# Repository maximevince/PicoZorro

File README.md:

# PicoZorro

An RP2350 microcontroller on the Amiga **Zorro II** bus. PIO state machines
speak the bus protocol, XRDY inserts wait states while the firmware fetches
the data, and the card's registers appear in the Amiga's address space
through Autoconfig. No CPLD, no FPGA, no level shifters. Open hardware,
open firmware, open drivers.

The first card is the **PicoZorro One**: Ethernet, a USB host port and an
MP3 decoder for an A2000-class Zorro II slot. Its through-hole version, the
**PicoZorro One TH**, is built from off-the-shelf modules and a handful of
through-hole parts, so that anyone with a soldering iron can make one.

| What | How | Amiga side |
|---|---|---|
| Ethernet 10/100 | W5500 module on SPI | `picozorro.device`, a SANA-II driver (Roadshow, AmiTCP, ...) |
| USB host (full speed) | the RP2350's USB port | `picozorrousb.device` for Poseidon |
| MP3 / MP2 decoding | minimp3 on the card | `mpega.library`, a drop-in replacement for the 68k one |
| Boot ROM | the drivers served from the card | nothing to install: Kickstart loads them at boot |
| Firmware updates | A/B partitions in the module's flash | `pzflash` on the Amiga |

## One TH: two builds, one board

The One TH PCB carries two parts lists. Every through-hole part has an SMD
alternate on the same nets, in the same footprint area, and only one of
the two is ever fitted. Same Gerbers, same firmware, same Amiga software.

| DIY build (all through-hole) | JLC build (SMD set assembled by JLCPCB) |
|---|---|
|  |  |
| KiCad's default variant. You solder everything: 1N5817, radial PTC, 2N3904, axial resistor, LD1117V33 in TO-220, electrolytics, a microSD breakout. | KiCad variant `JLC`. JLCPCB places SS14, 1812 PTC, MMBT3904, 0603 resistors, an AMS1117-3.3 (SOT-223) and banks of 22 uF MLCCs, plus a Hirose push-push microSD socket. You solder only the modules on their headers and the USB connector (J2 or J3). |
| Parts list: `fab/picozorro-one-th-parts.csv` | BOM and placement: `fab/jlc/picozorro-one-th-bom-jlc.csv`, `fab/jlc/picozorro-one-th-cpl-jlc.csv` |

Both builds take the same bought modules (Core2350B0, W5500 "Lite", the
optional GY-PCM5102 DAC). The silk frames each through-hole / SMD pair
under one label, so the board reads the same either way. Order options,
the full part-by-part table and the LCSC numbers are in
`hardware/picozorro-one-th/README.md` and `fab/order-notes.txt`.

## Status

- Firmware and drivers run on a prototype (a Core2350B module on a carrier
  board) in an Amiga: Ethernet, USB mass storage, MP3 playback.
- The **PicoZorro One TH** board is designed, routed and passes ERC/DRC.
  It has **not been built yet**. Do not order boards until this says so.
- The default firmware build is the One's image (features `xrdy-direct`,
  `int-nfet`, `usb-host`); the One TH and the One SMD share one pin map
  and one image. The four pins that differ from the prototype
  (microSD chip select, I2S) are unused, and the text log on GPIO46 lands
  on the DAC's bit-clock pin, which is harmless while no DAC is fitted.
- microSD and the I2S DAC are on the board for later; no firmware uses
  them yet.

## Repository

| Path | What |
|---|---|
| `hardware/picozorro-one-th/` | KiCad project, fabrication files, parts list and design notes of the One TH |
| `hardware/lib/` | the PicoZorro KiCad library (the Zorro II edge connector) |
| `hardware/EDGE_CONNECTOR.md`, `hardware/PINMAP.md` | edge-connector orientation with its evidence; the GPIO map |
| `firmware/` | RP2350 firmware in Rust on embassy: `pz-core` (Autoconfig, register window, network model, host tests), `pz-hal`, `pz-app` (the `picozorro` image, `hello`, `nic-demo`, `bus-listen`) |
| `amiga/` | the Amiga drivers, `mpega.library`, `pzflash`, the boot ROM, test and diagnostic tools; built with bebbo's GCC in docker |
| `tools/` | firmware image tools: update file, boot image, flashing |
| `docs/` | the register interface (`REGISTERS.md`, `REGISTERS-USB.md`, `REGISTERS-MPEG.md`), firmware updates (`UPDATE.md`), Zorro II electrical facts |

## From a bare board to a network

1. Build the card: `hardware/picozorro-one-th/README.md` (parts list,
   fabrication files, what to check before the first power-up).

   Steps 2 and 3 can be skipped: each
   [release](https://github.com/maximevince/PicoZorro/releases) carries
   `picozorro-install.uf2`, `picozorro.pzf` and the Amiga software, built
   by CI (`.github/workflows/build.yml`).
2. Build the Amiga software once, it goes into the firmware's boot image:

       make -C amiga toolchain   # once: pulls the image, fetches NDK 3.2 and the Poseidon headers
       make boot                 # drivers + boot ROM -> firmware/boot.img

3. Build and install the firmware, module on the bench, not in the Amiga:

       make fw-uf2               # firmware/picozorro-install.uf2

   Hold BOOTSEL while plugging the module's USB into the PC and copy
   `picozorro-install.uf2` onto the USB drive that appears. With an SWD
   probe, `make fw-install` does the same over SWD. This writes the A/B
   partition layout, so later updates come from the Amiga
   (`docs/UPDATE.md`), no cable needed. The UF2 route has not been
   exercised on a module yet; the SWD route has.
4. Card in the slot, Amiga on. Kickstart finds the card (manufacturer 2011,
   product $5A), loads `picozorro.device`, `picozorrousb.device` and
   `mpega.library` from it. Point your TCP/IP stack at `picozorro.device`
   unit 0 and Poseidon at `picozorrousb.device`: `amiga/README.md`.

Other targets: `make` (host tests + every firmware binary), `make amiga`,
`make fw-uf2 BIN=hello` (a first-light image as UF2), `make check-one-th`
(ERC + DRC). Needs: rustup (stable; the toolchain file adds the target),
arm-none-eabi-gcc (the MP3 decoder is C), picotool, probe-rs with RP2350
support for SWD, cargo-binutils for the update and install files; for `make amiga`:
docker, lha (or 7z), curl. Details in `firmware/README.md` and `amiga/README.md`.

## Safety

The card sits on the CPU bus of a machine that is not made any more.
Open-collector lines (XRDY, /INT2, /INT6) are never driven high. The
edge-connector orientation is documented with its evidence in
`hardware/EDGE_CONNECTOR.md`; check it against your board before powering
anything.

## Why the RP2350 sits on the 5 V bus without level shifters

The Zorro II bus is 5 V TTL. The RP2350's GPIO0-39 are fault-tolerant pads:
Raspberry Pi specifies them to 5.5 V **as long as IOVDD (the chip's 3.3 V)
is powered**. With IOVDD at 0 V the same pad is only rated to 3.63 V, and the
datasheet says a pad above that with IOVDD off will be damaged. So the whole
question is the first milliseconds after switch-on: can the bus be above
3.63 V before the card's 3.3 V regulator has come up?

Reasoning first: the bus drivers and pull-ups are fed from the same +5 V
rail that feeds the card's regulator, so no bus line can be ahead of that
rail. Below regulation an LDO just passes its input minus a drop, so IOVDD
follows the rail closely. The datasheet's limit only bites if the regulator
*delays* its start by more than the time the rail needs to travel from where
the LDO can start (about 2.3 V) to 3.63 V.

Then measured, with a logic analyser's analog channels:

- An Amiga's Zorro +5 V rises to 5.1 V in 3.4 ms; **2.3 V to 3.63 V takes
  about 1 ms**, 3.63 V to 4.2 V another 0.5 ms.
- The Core2350B's regulator (ME6217, 3.3 V), hit with a hard 5 V step on its
  input as the worst case: **3V3 reaches 3 V about 50 us later.**

50 us against 1 ms is a 20x margin, and on the real ramp the regulator does
not even see a step. IOVDD is therefore always above 1.8 V when the bus
passes 3.63 V and above 2.5 V when it passes 4.2 V, which is what the
datasheet's rating table asks for. The silicon on the module is an A4
stepping, the one Raspberry Pi qualified as 5 V tolerant; the erratum that
made A2 parts leak (RP2350-E9) is fixed from A3 on.

What this does **not** cover: hot-plugging a card into a live machine, or a
card whose 3.3 V rail is dead while the bus is up. Both put 5 V on unpowered
pads. Don't.

## Licence

Copyleft on purpose: forks stay open.

- Firmware, tools and the Amiga software: **GPL-3.0-or-later**
  (`LICENSES/GPL-3.0-or-later.txt`). The Rust dependencies (embassy and
  friends, MIT / Apache-2.0) are compatible. Vendored code keeps its own
  licence: `firmware/vendor/`.
- Hardware (`hardware/`): **CERN-OHL-S-2.0**, strongly reciprocal
  (`LICENSES/CERN-OHL-S-2.0.txt`).
  Three of the 3D models in `hardware/picozorro-one-th/3d/` embed parts of
  the KiCad library and are CC BY-SA 4.0 with KiCad's exception
  (`3d/SOURCES.txt`).
- Documentation: **CC BY-SA 4.0** (`LICENSES/CC-BY-SA-4.0.txt`).

Copyright Maxime Vincent.

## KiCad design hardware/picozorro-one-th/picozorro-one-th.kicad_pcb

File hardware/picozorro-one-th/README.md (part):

# PicoZorro One TH

The PicoZorro One is the Zorro II network and USB card of the PicoZorro
project. The One TH is its through-hole version: bought modules and a
handful of through-hole parts on a bare two-layer PCB. Every through-hole
part also has an SMD alternate on the same board, so the same PCB can be
assembled by JLCPCB instead (see "Two builds" below).

- RP2350B: a Waveshare Core2350B0 module (B0 variant, no PSRAM) on four
  2x8 pin strips. Its PIO state machines speak the Zorro II bus directly.
- Ethernet: a W5500 "Lite" module (USR-ES1, WIZnet WIZ850io pinout) on SPI1.
- USB host: the RP2350's own USB port, to a type A receptacle or a PC-style
  2x5 internal header.
- Optional: microSD on SPI1 (a breakout, or a soldered socket on the JLC
  build) and a GY-PCM5102 I2S DAC breakout.

## Status

Rev A. The schematic and the routed board pass KiCad ERC and DRC with zero
violations, DRC with schematic parity (`make check-one-th` at the top of the
repository). **The board has not been built or tested in an Amiga. Do not
order boards yet.** The open points are listed at the end of this file.

## Two builds: DIY through-hole and JLC-assembled

One PCB, two builds. The **DIY build** (KiCad's default variant) fits every
part through-hole, soldered by hand. The **JLC build** (KiCad variant `JLC`)
has JLCPCB place an SMD set, almost all JLC Basic parts; the builder then
solders only the modules on their headers and J2 (or J3).

Each through-hole part and its SMD alternate sit on the same nets and share
the footprint area; the two are never both fitted. The SMD alternate of a
part has the part's number times 100 plus 1, 2, ... as its reference (D101 is
D1's, C101-C103 are C1's bank), because KiCad cannot give one symbol two
footprints. The board hides those references; silk frames group each pair
under one label, and the JLC files name them "D1 (SMD)".

## Files

| Path | What |
|---|---|
| `picozorro-one-th.kicad_pro`, `.kicad_sch`, `.kicad_pcb`, `.kicad_dru` | KiCad 10 project with the variant `JLC`; the edge-connector symbol and footprint come from `../lib` |
| `fab/gerbers/`, `fab/picozorro-one-th-gerbers.zip` | Gerber and Excellon drill files, the same for both builds |
| `fab/picozorro-one-th-parts.csv` | parts list of the DIY build (the SMD alternates show DNP) |
| `fab/jlc/picozorro-one-th-bom-jlc.csv`, `fab/jlc/picozorro-one-th-cpl-jlc.csv` | JLC BOM (the SMD set with LCSC numbers; the through-hole alternates as DNP) and placement file (SMD set only, rotations corrected for JLC) |
| `fab/order-notes.txt` | the options to pick in the order form, and what the builder solders in each build |
| `3d/` | STEP models of the modules and the PTC that the board references; origins and licences in `3d/SOURCES.txt` |
| `images/` | schematic (PDF, PNG), copper and silkscreen views, 3D renders: `pcb-3d-th.png` (DIY build), `pcb-3d-jlc.png` (JLC build, same view), `pcb-3d-iso.png` (DIY build, isometric) |

## What the builder solders

DIY build, everything by hand. The last column names the SMD alternate the
JLC build fits instead (LCSC part number in brackets; JLC Basic parts unless
marked Extended).

| Ref | Part | Value / type | Package | Fitted (DIY) | JLC build alternate |
|---|---|---|---|---|---|
| U1 (P1-P4) | Waveshare Core2350B0 module (no PSRAM) | - | four 2x8 2.54 mm pin strips | yes | same, by hand |
| M1 | W5500 "Lite" module (USR-ES1, WIZ850io pinout) | - | two 1x6 2.54 mm rows | yes | same, by hand |
| M2 | microSD breakout, 3.3 V, no level shifter | - | one 1x6 2.54 mm row | optional | J6, Hirose DM3AT-SF-PEJM5 push-push socket (C114218, Extended), with R2-R5 and C5, C6 |
| M3 | PCM5102A DAC breakout "GY-PCM5102" | - | 1x6 row (signals) + 1x9 row (holding only) | optional | same, by hand (optional) |
| D1 | Schottky diode | 1N5817 | DO-41, 10.16 mm | yes | D101, SS14, SMA (C2480) |
| F1 | resettable PTC fuse, 30 V (or 16 V) family | 0.9 A hold, e.g. Littelfuse RUEF090 | radial, 5.08 mm leads | yes | F101, 1.1 A hold, 1812, Littelfuse 1812L110/33MR (C142747, Extended) |
| C1 | electrolytic capacitor, bus +5 V | 100 uF | radial, D6.3 mm, 2.5 mm pitch | yes | C101-C103, 3 x 22 uF 25 V X5R 1206 (C12891) |
| C2 | electrolytic capacitor, USB port | 220 uF | radial, D8 mm, 3.5 mm pitch | yes | C201-C205, 5 x 22 uF 25 V X5R 1206 (C12891) |
| U2 | 3.3 V regulator for 3V3_AUX | LD1117V33 | TO-220, lying down | yes | U201, AMS1117-3.3, SOT-223, tab = VOUT (C6186) |
| C3 | U2 input capacitor | 10 uF 25 V electrolytic | radial, D5 mm, 2 mm pitch | yes | C301, 10 uF 25 V X5R 0805 (C15850) |
| C4 | U2 output capacitor | 10 uF | disc, 5 mm pitch | yes | R6 1.0 ohm 0603 (C22936) in series with C401 22 uF 1206 (C12891) |
| Q1 | NPN transistor | 2N3904 | TO-92, E-B-C | yes | Q101, MMBT3904, SOT-23, 1 B / 2 E / 3 C (C20526) |
| R1 | resistor, GPIO45 to Q1 base | 2.2 k | axial, DIN0207, 10.16 mm | yes | R101, 2.2 k 0603 (C4190) |
| J2 | USB 2.0 type A receptacle, right angle | Molex 67643 pattern | through-hole | one of J2 / J3 | same, by hand |
| J3 | PC internal USB header | 2x5, pin 9 absent | 2.54 mm header | one of J2 / J3 | same, by hand |
| J4 | SWD header: SWCLK / GND / SWDIO | - | 1x3 2.54 mm | no (developers) | same |
| J5 | recovery header: RUN / GND / BOOTSEL | - | 1x3 2.54 mm | no (recovery) | same |

The JLC build adds, with J6 only: R2-R5, 10 k 0603 pull-ups on DAT2, CMD
(MOSI), DAT0 (MISO) and DAT1 (C25804); C5 100 nF 0603 (C14663) and C6
10 uF 0805 (C15850) at J6's VDD.

U1 must be the B0 variant in both builds: on the B1 / B2 modules GPIO47 is
the PSRAM chip select, and this board needs GPIO47 for the I2S word clock.
The microSD chip select (GPIO18) works on any variant.

The parts lists are `fab/picozorro-one-th-parts.csv` (DIY) and
`fab/jlc/picozorro-one-th-bom-jlc.csv` (JLC).

F1 alternatives: Littelfuse RUEF090 or 30R090U, Bourns MF-R090-0-9,
Littelfuse RUSBF090 (0.07-0.12 ohm new, 0.22 ohm at most after a trip;
holds 0.57-0.61 A at 60 C). Not the 0.5 A hold parts: they hold 0.36 A at
50 C and drop up to 0.59 V. The footprint is KiCad's
`Fuse_Bourns_MF-RHT070` (5.1 mm lead spacing with the 1.2 mm stagger of a
radial PTC's leads, 0.71 mm holes for 0.51 mm leads); the KiCad library
has no footprint for the parts named above.

Q1 alternatives: the footprint is three holes in line, base in the middle,
emitter - base - collector as pins 1-2-3.

| Part | Pin order 1-2-3 | Fits |
|---|---|---|
| 2N3904, PN2222A, 2N4401, S8050 | E-B-C | as drawn |
| BC547, BC548, BC337 | C-B-E | rotated 180 degrees (silkscreen: "BC547 C-B-E: turn round") |

Only the 2N3904 and the BC547 were checked against a data sheet; check the
others before fitting.

U2 alternatives (pin order GND / VOUT / VIN seen from the front, tab =
VOUT): LD1117V33, LM1117T-3.3, AZ1117T-3.3, LM1086CT-3.3, LT1086CT-3.3.
They do not fit with VIN and VOUT swapped, middle pin GND, tab GND: LF33CV,
LM3940IT-3.3, MCP1825S, MCP1826S. The silkscreen names the three holes.
C3 is an electrolytic: mind its polarity.

## Solder jumpers

| Jumper | As delivered | Change |
|---|---|---|
| JP1 | bridged 1-2 by a trace: Q1 collector to /INT2 (J1 pin 19) | cut 1-2 and bridge 2-3 for /INT6 (J1 pin 22) |
| JP2 | **open** in both builds: U2 (DIY) or U201 (JLC) supplies 3V3_AUX | fallback for a board without U2: bridge it, and the module's 3V3 (U1 P2.16) feeds 3V3_AUX. Never bridge it with U2 or U201 fitted |

## Pin map

The PicoZorro GPIO map (`../PINMAP.md`) applies to GPIO0-17, 19-43 and 45.
Four pins differ on this board:

| GPIO | Module pin | Shared map | This board |
|---|---|---|---|
| 18 | P3.6 | /LDS | microSD chip select |
| 44 | P4.15 | /ARM | I2S data (DIN) |
| 46 | P2.4 | UART0 TX | I2S bit clock (BCK) |
| 47 | P2.3 | not connected / PSRAM chip select | I2S word clock (LCK), B0 module only |

The whole map:

| GPIO | Signal | Goes to |
|---|---|---|
| 0-15 | D0-D15 | J1 |
| 16 | /AS | J1 74 |
| 17 | /UDS | J1 72 |
| 18 | SD_CS | M2 pin 2 / J6 DAT3 |
| 19 | READ | J1 68 |
| 20-26 | A1-A7 | J1 |
| 27 | XRDY | J1 18, direct |
| 28-35 | A16-A23 | J1 |
| 36 | /CFGIN | J1 12 |
| 37 | /CFGOUT | J1 11 |
| 38 | /BUSRST | J1 94 |
| 39 | NIC_INT | M1 INTn (the module's LED1 is on the same pin, lit while INTn is high) |
| 40 | SPI1 MISO | M1, M2 / J6 DAT0 |
| 41 | NIC_CS | M1 SCSn |
| 42 | SPI1 SCK | M1, M2 / J6 CLK |
| 43 | SPI1 MOSI | M1, M2 / J6 CMD |
| 44 | I2S_DIN | M3 |
| 45 | INT_DRV | R1 / R101, Q1 / Q101 base |
| 46 | I2S_BCK | M3 |
| 47 | I2S_LCK | M3 |

Bus signals use only GPIO0-38 (5 V tolerant); GPIO39-47 never see the bus.
The bus nets go straight from the edge fingers to the module pins: no series
resistors, no buffers. XRDY comes from GPIO27 directly (36 ns from /AS to
XRDY measured at 240 MHz). The edge connector (J1) has +5 V on pins 5 and
6, all GND pins connected and pin 91 tied to GND.

There is no UART: debug is SWD with RTT on J4.

**/LDS (J1 pin 70) is not connected.** The bus PIO programs wait on /AS and
branch on READ only; the strobes are two bits of the sampled word, used by
the register model to tell word from byte access. With /UDS alone, word
access, Autoconfig (its writes are /UDS-only bytes on D15-D8) and the
rejection of an odd-byte write (/UDS high) work; an even-byte write cannot be
told from a word write and is taken as a word write.

**GPIO47 and the module variant.** On the Core2350B B1 / B2 modules the PSRAM
chip select sits directly on GPIO47 with a 10 k pull-up (R9); R11 (0 R) only
links the net to header pin P2.3. Driving GPIO47 there selects the PSRAM
during flash access. I2S therefore needs the B0 module, and the firmware
must not drive GPIO47 unless a PSRAM probe has found none.

### Firmware

The default firmware build is this board's image: its features
`xrdy-direct` (GPIO27 pulls XRDY) and `int-nfet` (GPIO45 push-pull, high
asserts /INT) match the bus side. The One TH and the One SMD share one pin
map and one image. GPIO18 / 44 / 46 / 47 may only be driven by a firmware
built for this board. The microSD and I2S
drivers are not written yet. When they are:

- SPI1 is shared. The SD card releases its data output one clock after its
  chip select rises, so the firmware clocks one byte with both chip selects
  high before selecting the W5500; each device gets its own SCK rate.
- An SD card that has not been put into SPI mode still listens to the
  command line. The firmware initialises the card before network traffic
  starts; a card inserted later sees W5500 traffic first.
- I2S is enabled only after a PSRAM probe has found none.

## Power

```
J1 +5V --+-- C1 --GND
         |
         +-- D1 -->|-- VIN ---- U1 P2.15 (VBUS: module LDO input)
         |                 +--- M3 VIN
         |
         +-- F1 ---+--- VBUS_PORT --- J2.1, J3.1, J3.2
         |         +--- C2 --GND
         |
         +-- C3 --- U2 --- C4 --- 3V3_AUX --- M1, M2 / J6

U1 P2.16 (3V3, module LDO output) --- JP2 (open; bridged only without U2) --- 3V3_AUX
```

JLC build: D101, F101 and U201 (C301 at its input, R6 + C401 at its output)
in place of D1, F1 and U2 (C3, C4); the bulk is two MLCC banks, C101-C103 on
the bus +5 V for C1 and C201-C205 on VBUS_PORT for C2 (40.9 and 68.2 uF
effective at 5 V). JP2 stays open in both builds.

- **D1** (Schottky) keeps bench power off the Amiga's +5 V rail: the
  module's FPC USB adapter feeds the same VBUS net.
- **F1** (PTC) is all there is between the bus +5 V and the USB port, as on
  PC motherboards (Intel 815E reference board; Intel, "Power Delivery Design
  Issues for Hi-Speed USB on Motherboards") and the fuse-only hobby host
  boards. No series diode (with a Schottky the port sat at about 4.45 V), no
  power switch IC.
- The card is powered by the Amiga, or by the FPC adapter on the bench. The
  port never powers the card.
- Not protected: a hub that feeds its own 5 V back into the port reaches the
  Amiga's +5 V rail through F1, also with the Amiga switched off. USB 2.0
  section 7.2.1 forbids a device to source current on its upstream port.

Port voltage from a 5.0 V rail at 500 mA: 5.0 - 0.06 (F1 new, 0.11 after a
trip) = 4.94 V (4.89 V). USB 2.0 Table 7-7 asks for 4.75 V at a high-power
port, so the rail may sag to 4.86 V. Section 7.2.1.2.1 asks for
resettable over-current protection below 5.0 A: F1 trips at 1.8 A (Intel's
guide sizes a single-port fuse at 1.5 A trip or more). The fault is not
reported to the host stack: there is no pin for it.

### Bulk: C1 and C2

USB 2.0 section 7.2.4.1 asks for no less than 120 uF of low-ESR capacitance
on the downstream VBUS "per hub", to keep the power of the other ports
within 330 mV when a device is plugged in (load model 10 uF with 44 ohm).
This card has one port: the only other load on that VBUS is the card's own
+5 V entry (D1 to VIN, U2) and, behind it, the Amiga rail. So both stay: C1
at the entry, C2 at the port, F1 between them (on a microsecond scale the
PTC is a plain resistor that isolates the two).

A hot-plug simulation (1 m cable, assumed rail and ESR values, not a
measurement) puts the entry droop at 0.23 / 0.15 V (PTC 0.1 / 0.3 ohm) with
the JLC build's ceramic banks, the smallest of the arrangements tried at
0.3 ohm, matched only by a low-ESR polymer 220 uF at the entry (0.22 /
0.17 V). The DIY build's two electrolytics give 0.43 / 0.29 V; a single
ordinary electrolytic at the entry (0.15 ohm ESR) 0.61 / 0.45 V, worse than
either split. The port itself dips 0.4 to 3 V for microseconds whatever is
fitted: no arrangement holds it within 330 mV with a stick plugged straight
in. Both builds lay the two groups out alike: the electrolytic on top, its
MLCC row under it in the 15 mm band.

### 3.3 V

3V3_AUX (M1, M2 / J6) has its own regulator, **U2, fitted in both builds**;
JP2 stays open and the module's LDO feeds only the module. The loads: M1
132 mA typical (W5500 data sheet section 5.4; the WIZ850io module 141 mA),
M2 up to 100 mA, the maximum averaged over 1 s in SPI mode (SD Physical
Layer Simplified Specification v3.01, Table 3-4 note 7; SanDisk's manual
gives 65 mA read and 75 mA write at most). The simplified specification
gives no peak or inrush figure. That is about 0.22 A typical, 0.24-0.27 A
at those ceilings. M3 is not on this rail: its VIN comes from VIN and it has
its own two regulators.

U2 takes the bus +5 V directly, not behind D1. DIY build: LD1117V33. ST
guarantees 3.235-3.365 V out for Vin 4.75-10 V at 0-800 mA (TJ 0-125 C,
LD1117 data sheet DocID2572 Rev 38, Table 6), dropout 1.15 V at most at
500 mA: it regulates from 4.45 V, a 0.30 V margin at the bus's 4.75 V
minimum. The JLC build fits U201, an AMS1117-3.3 (SOT-223, the same pin
order, tab = VOUT) under U2's footprint, its tab on the same 3V3_AUX copper
area. Its only guaranteed dropout is 1.3 V at 800 mA, so it needs 4.60 V: a
margin of about 0.15 V. R6 (1.0 ohm) in series with C401 (22 uF) at its
output gives the ceramic the ESR of the tantalum the AMS1117 data sheet is
written for. Dissipation in either build: (5.25 V - 3.3 V) x 0.3 A = 0.59 W
at most.

- C3, 10 uF at the input in both builds (DIY: 25 V radial electrolytic;
  JLC: C301, 0805 X5R): one value that satisfies the LD1117 (100 nF), the
  LM1117 and AZ1117 (10 uF) and the AMS1117 application circuit (10 uF). C4,
  10 uF at the output (ST's figure; ST gives no ESR window).
- With U2 fitted and the card on bench power only, M1 and M2 are unpowered
  while the module runs.

The module's regulator is the fallback (JP2 bridged on a board without
U2), not the default: the ME6217C33M5G data sheet gives 800 mA as a typical
IOUT(max) (and as the absolute maximum), no minimum, and notes it may not be
reached because of package dissipation; it gives no thermal resistance. Its
sibling ME6207 rates the SOT-23-5 package at 250 mW. The W5500 alone puts
0.25-0.41 W into it, with an SD card 0.45-0.66 W. Measured with a thermal
camera, module plus W5500 on the module's 3V3, room 20 C: nothing on the
module above 40 C (no SD card in that measurement).

There is no extra bulk capacitance on VIN or 3V3: it would slow the 3V3
rise against the Amiga's +5 V ramp.

## /INT driver

Q1, an NPN transistor, drives the interrupt line open collector: emitter to
GND, base through R1 (2.2 k) to GPIO45, collector through JP1 to /INT2
(default) or /INT6. GPIO45 high asserts the interrupt. GPIO45 resets with
its pull-down on, so Q1 is off while the module is in reset; with the module
absent the base is open and Q1 is off. GPIO45 is not 5 V tolerant, so it
cannot pull the bus line itself.

Sizing: a B2000 and an A500+ pull both lines up with 1 k (5 mA at 5 V); the
Technical Reference Manual's open-collector drive class is 0.5 V at 8 mA,
so the driver must sink at least 8 mA. R1 gives (3.3 - 0.75) / 2.2 k =
1.2 mA of base current. The 2N3904 is specified at VCE(sat) 0.2 V maximum
for 10 mA with 1 mA into the base, the BC547 at 0.25 V maximum (0.09 V
typical) for 10 mA with 0.5 mA: both operating points are covered with
margin.

A transistor and not a MOSFET: the through-hole MOSFETs hobby shops carry
(2N7000, BS170) have gate thresholds up to 3 V and are not specified at
3.3 V drive; the one that is (TN0702) is a distributor-only part. Small NPN
types are sold everywhere.

Simulated with ngspice (vendor models, 1 k to 10 k pull-ups, 4.75 to
5.25 V, 0 to 70 C, GPIO45 down to 3.0 V, R1 +5 %): /INT sits below 90 mV
with a 2N3904 and below 40 mV with a BC547B, also at a forced 8 mA;
GPIO45 sources 1.15 mA at most. Assertion takes under 125 ns into 1 nF.
Release is the pull-up RC plus the transistor's storage time: 0.25 to
0.5 us for the 2N3904, 1.4 to 2.2 us for the BC547B, so 10 k with 500 pF
reaches 2.0 V after 3.2 us (2N3904) or 4.9 us (BC547B). The 2N3904 is the
default for that reason.

## Modules

**M1, W5500 Lite.** Two 1x6 rows, 2.54 mm pitch, 20.32 mm apart; module
23.0 x 25.0 mm; pin 1 of each row at the jack-opening end, 6.4 mm from that
edge; the jack overhangs that edge by 2.5-2.7 mm. Seen from the top with the
jack opening away from the viewer (module silk J1 left, J2 right, jack
HR961160C):

| Left row (J1) | | Right row (J2) | |
|---|---|---|---|
| 1 GND | GND | 1 GND | GND |
| 2 GND | GND | 2 3.3V | 3V3_AUX |
| 3 MOSI | GPIO43 | 3 3.3V | 3V3_AUX |
| 4 SCLK | GPIO42 | 4 NC | - |
| 5 SCNn | GPIO41 | 5 RSTn | not connected |
| 6 INTn | GPIO39 | 6 MISO | GPIO40 |

RSTn stays open: the module has its own power-on reset (10 k, 100 nF,
1N4148) and the firmware resets the chip in software. The module has 10 k
pull-ups on SCSn and INTn, so the W5500 is deselected while the RP2350 is
in reset.

**M2, microSD breakout.** One 1x6 row: 3V3 (pin 1, to 3V3_AUX), CS (GPIO18),
MOSI (GPIO43), CLK (GPIO42), MISO (GPIO40), GND. Board 18 x 18 mm (18.1 mm
over its scored edges); the socket, 13.7 mm wide, overhangs the edge
opposite the pin row by 3 mm and the card enters from there. No pull-up on
the chip select: GPIO18 resets with its pull-down on (about 50-80 k), which
selects the card while the RP2350 is in reset; nothing is clocked then, and
the firmware drives the chip select high as soon as it has configured its
GPIOs, before it uses SPI1. The breakout carries four 10 k pull-ups of its
own, on lines not identified.

**J6, microSD socket (JLC build).** A Hirose DM3AT-SF-PEJM5 push-push socket
(KiCad `Connector_Card:microSD_HC_Hirose_DM3AT-SF-PEJM5`) under M2's
outline, on M2's nets, the card entering over the top edge as with M2: CS =
DAT3 (GPIO18), MOSI = CMD, CLK, MISO = DAT0, VDD = 3V3_AUX. 10 k pull-ups R2
(DAT2), R3 (CMD / MOSI), R4 (DAT0 / MISO), R5 (DAT1), none on CS; C5 100 nF
and C6 10 uF at VDD. Card detect (pins 9, 10) is not connected: no GPIO is
free. M2 and J6 are never both fitted.

**M3, GY-PCM5102.** The 6-pin row on its short edge: SCK to GND (selects the
PCM5102A's internal PLL), BCK to GPIO46, DIN to GPIO44, LCK to GPIO47, GND,
VIN to VIN. Pin 1 is SCK. The 9-pin row (FLT, DEMP, XSMT, FMT, A3V3, AGND,
ROUT, AGND, LROUT from the SCK corner) gets nine unconnected holes: it only
holds the board. Audio leaves through the breakout's 3.5 mm jack. The four
strap bridges on its underside stay as usually delivered: FLT low, DEMP
low, XSMT high, FMT low. BCK and LCK are on consecutive GPIOs so one PIO
side-set drives both; PLL mode accepts BCK = 32 fs or 64 fs from 32 kHz to
384 kHz. Geometry, from a third-party footprint (sstojos,
zynthian-miniature) cross-checked against board photos: board 31.6 x
17.0 mm; the 6-pin row 1.5 mm from the short edge; the 9-pin row 1.5 mm
from the long edge next to the SCK pin, its first hole (FLT) 6.35 mm along
the board from the 6-pin row and 0.635 mm outside the SCK hole.

## USB host port, debug and recovery

- The module's USB pins (D+ on P2.9, D- on P2.7, 27 R on the module) go to J2
  and J3 in parallel; only one of the two is fitted.
- **J2**: through-hole type A, right angle, the hole pattern shared by Molex
  67643, Stewart SS-52100-001, Kycon KUSBX-AS1N and Connfly DS1095. 1
  VBUS_PORT, 2 D-, 3 D+, 4 GND, shell to GND.
- **J3**: 2x5, pin 9 absent (key). 1 and 2 VBUS_PORT, 3 D-, 5 D+, 7 and 8
  GND; 4, 6 (a second port's data) and 10 (over-current sense on a PC) not
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
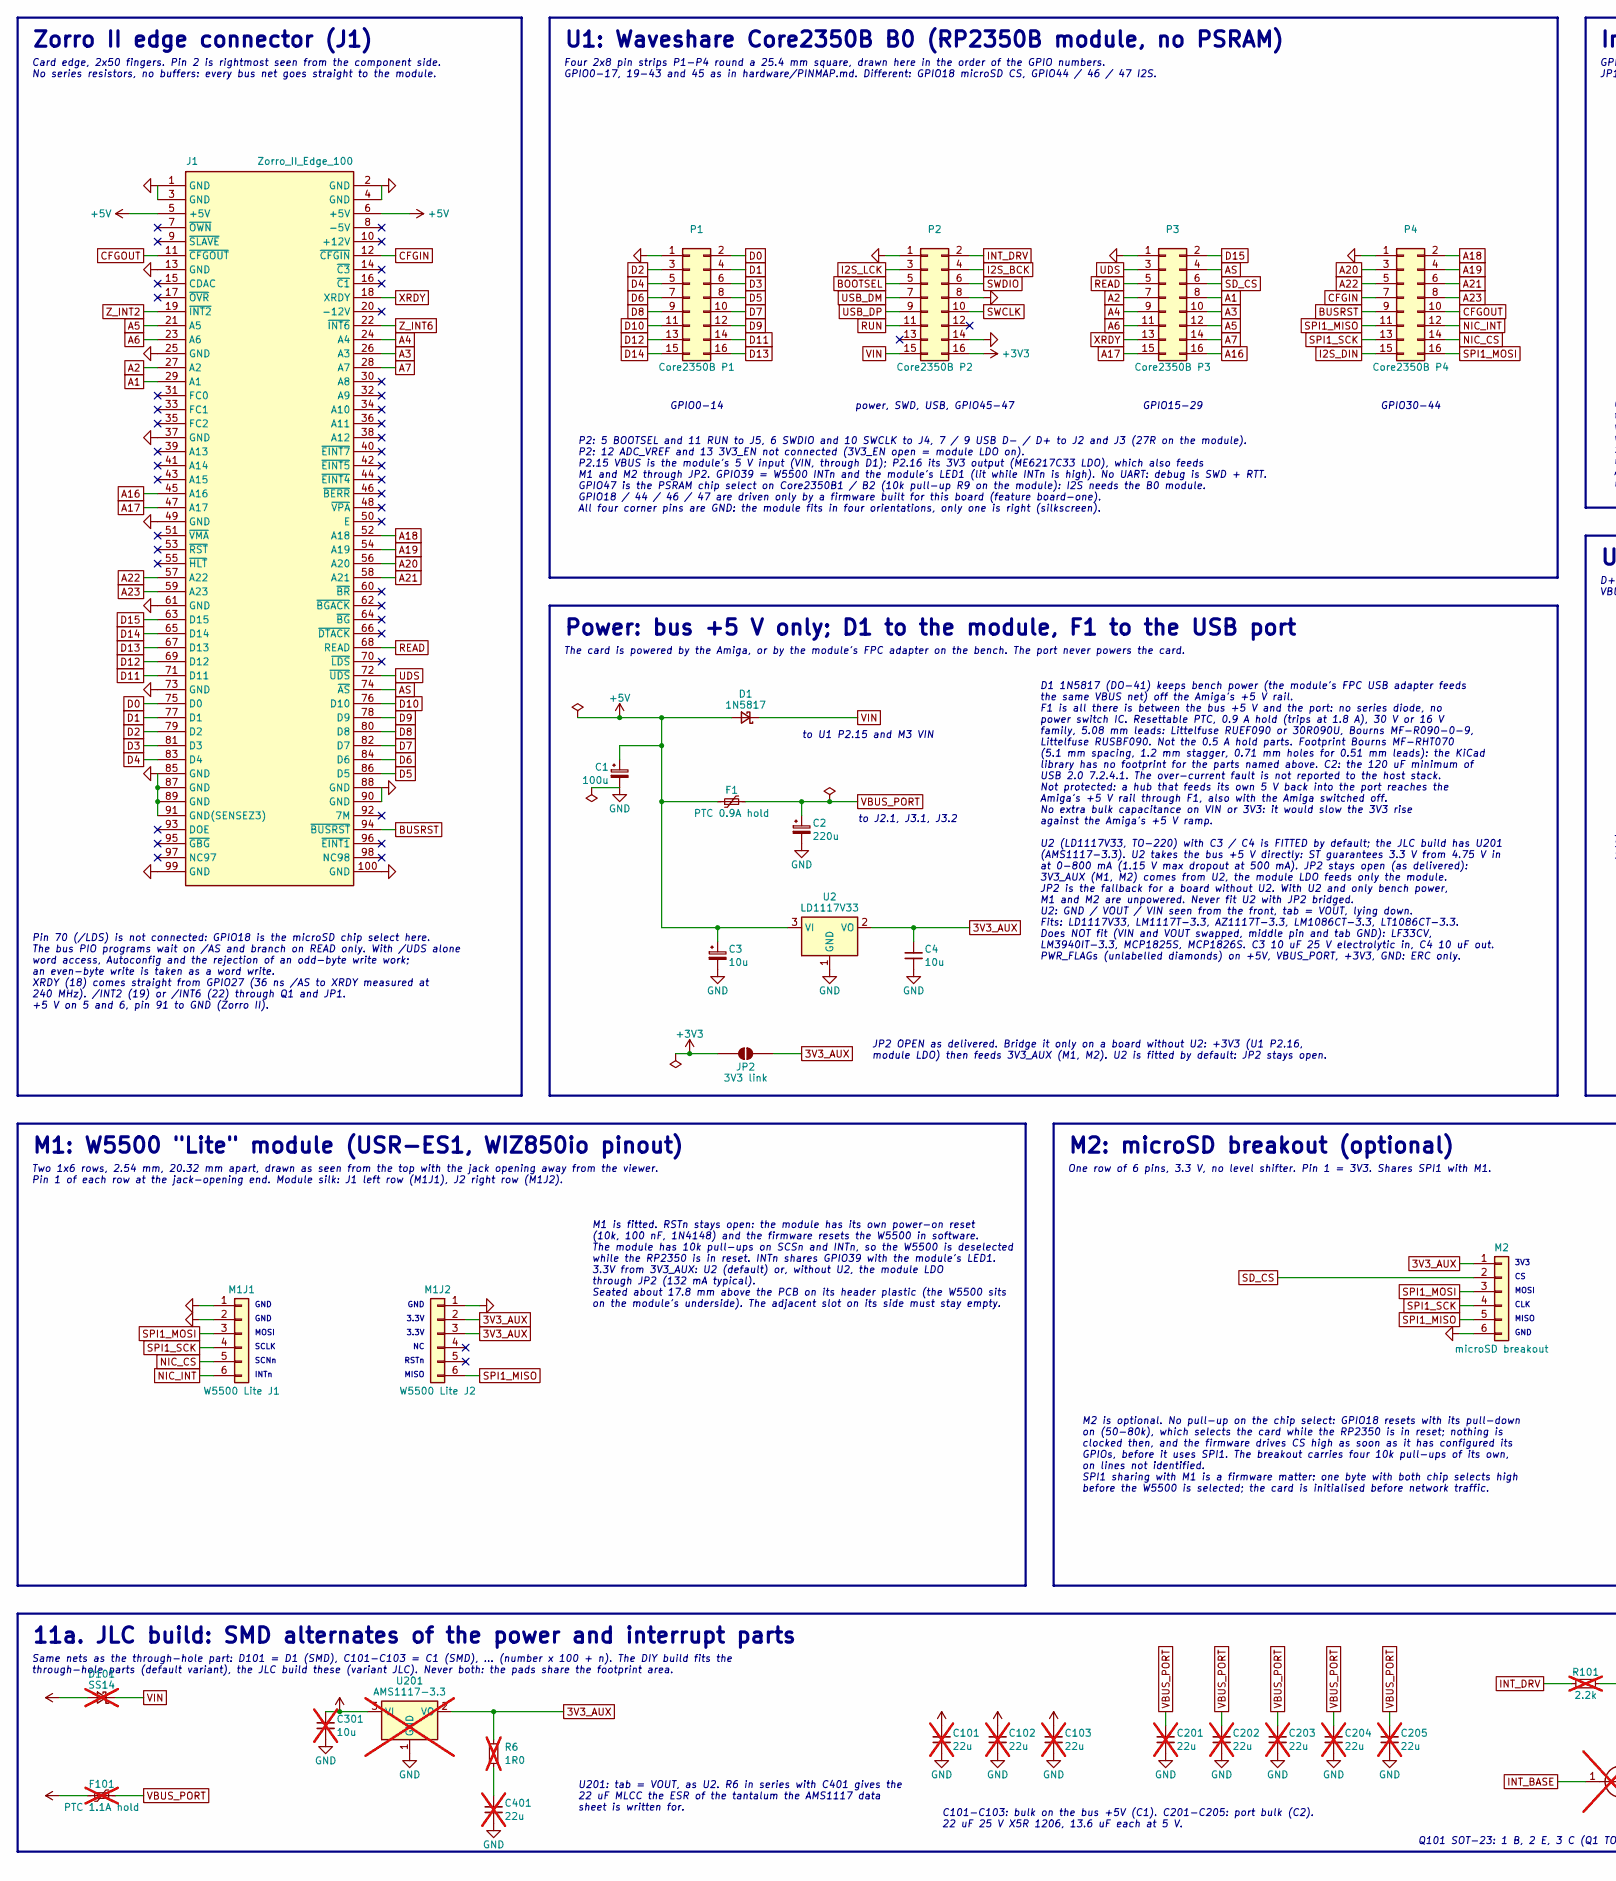
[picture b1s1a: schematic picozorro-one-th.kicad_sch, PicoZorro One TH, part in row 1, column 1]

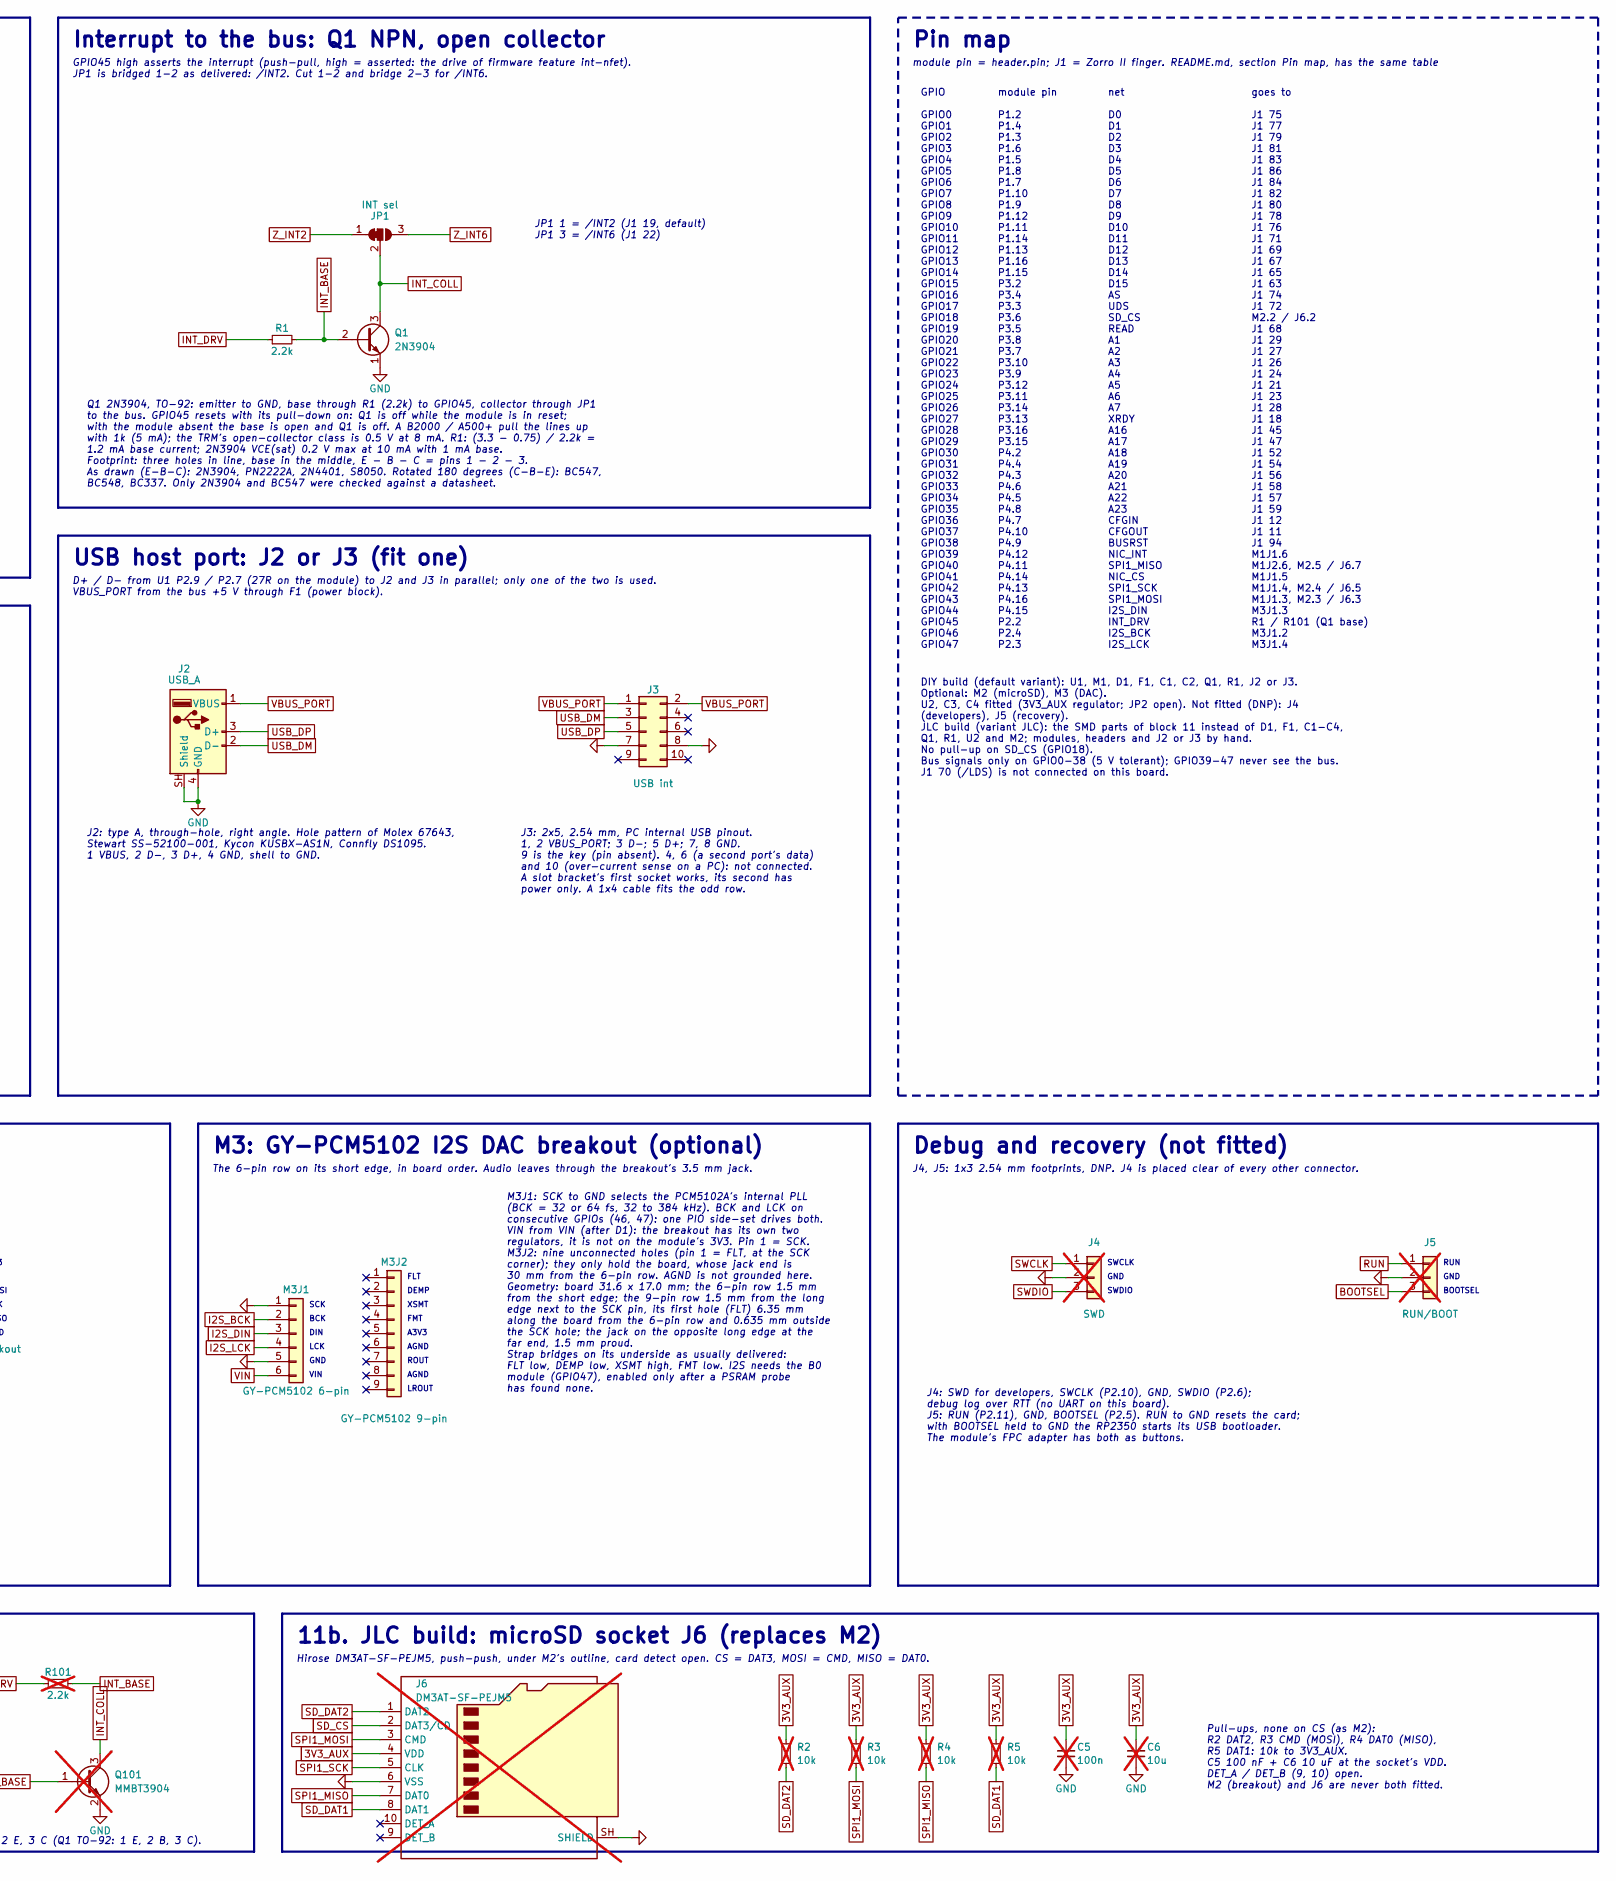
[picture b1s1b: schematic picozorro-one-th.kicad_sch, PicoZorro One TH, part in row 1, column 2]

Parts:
C1: 100u; CP_Radial_D6.3mm_P2.50mm
C2: 220u; CP_Radial_D8.0mm_P3.50mm
C3: 10u; CP_Radial_D5.0mm_P2.00mm
C4: 10u; C_Disc_D5.1mm_W3.2mm_P5.00mm
C5: 100n; C_0603_1608Metric; MPN CC0603KRX7R9BB104; LCSC C14663; not fitted
C6, C301: 10u; C_0805_2012Metric; MPN CL21A106KAYNNNE; LCSC C15850; not fitted
C101, C102, C103, C201, C202, C203, C204, C205, C401: 22u; C_1206_3216Metric; MPN CL31A226KAHNNNE; LCSC C12891; not fitted
D1: 1N5817; D_DO-41_SOD81_P10.16mm_Horizontal; MPN 1N5817
D101: SS14; D_SMA; MPN SS14; LCSC C2480; not fitted
F1: PTC 0.9A hold; Fuse_Bourns_MF-RHT070; MPN RUEF090
F101: PTC 1.1A hold; Fuse_1812_4532Metric; MPN 1812L110/33MR; LCSC C142747; not fitted
J1: Zorro_II_Edge_100
J2: USB_A; USB_A_Molex_67643_Horizontal
J3: USB int; PinHeader_2x05_P2.54mm_Vertical
J4: SWD; PinHeader_1x03_P2.54mm_Vertical; not fitted
J5: RUN/BOOT; PinHeader_1x03_P2.54mm_Vertical; not fitted
J6: DM3AT-SF-PEJM5; microSD_HC_Hirose_DM3AT-SF-PEJM5; MPN DM3AT-SF-PEJM5; LCSC C114218; not fitted
JP1: INT sel; SolderJumper-3_P1.3mm_Bridged12_RoundedPad1.0x1.5mm_NumberL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
JP2: 3V3 link; SolderJumper-2_P1.3mm_Open_RoundedPad1.0x1.5mm
M1J1: W5500 Lite J1; PinHeader_1x06_P2.54mm_Vertical
M1J2: W5500 Lite J2; PinHeader_1x06_P2.54mm_Vertical
M2: microSD breakout; PinHeader_1x06_P2.54mm_Vertical
M3J1: GY-PCM5102 6-pin; PinHeader_1x06_P2.54mm_Vertical
M3J2: GY-PCM5102 9-pin; PinHeader_1x09_P2.54mm_Vertical
P1: Core2350B P1; PinHeader_2x08_P2.54mm_Vertical
P2: Core2350B P2; PinHeader_2x08_P2.54mm_Vertical
P3: Core2350B P3; PinHeader_2x08_P2.54mm_Vertical
P4: Core2350B P4; PinHeader_2x08_P2.54mm_Vertical
Q1: 2N3904; TO-92_Inline; MPN 2N3904
Q101: MMBT3904; SOT-23; MPN MMBT3904; LCSC C20526; not fitted
R1: 2.2k; R_Axial_DIN0207_L6.3mm_D2.5mm_P10.16mm_Horizontal
R2, R3, R4, R5: 10k; R_0603_1608Metric; MPN 0603WAF1002T5E; LCSC C25804; not fitted
R6: 1R0; R_0603_1608Metric; MPN 0603WAF100KT5E; LCSC C22936; not fitted
R101: 2.2k; R_0603_1608Metric; MPN 0603WAF2201T5E; LCSC C4190; not fitted
U2: LD1117V33; TO-220-3_Horizontal_TabDown; MPN LD1117V33
U201: AMS1117-3.3; SOT-223-3_TabPin2; MPN AMS1117-3.3; LCSC C6186; not fitted

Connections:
3V3_AUX: C4.1, C5.1, C6.1, J6.4 (VDD), JP2.2 (B), M1J2.2, M1J2.3, M2.1, R2.1, R3.1, R4.1, R5.1, R6.1, U2.2 (VO), U201.2 (VO)
+3V3: JP2.1 (A), P2.16
+5V: C1.1, C3.1, C101.1, C102.1, C103.1, C301.1, D1.2 (A), D101.2 (A), F1.1, F101.1, J1.5 (+5V), J1.6 (+5V), U2.3 (VI), U201.3 (VI)
A1: J1.29 (A1), P3.8
A2: J1.27 (A2), P3.7
A3: J1.26 (A3), P3.10
A4: J1.24 (A4), P3.9
A5: J1.21 (A5), P3.12
A6: J1.23 (A6), P3.11
A7: J1.28 (A7), P3.14
A16: J1.45 (A16), P3.16
A17: J1.47 (A17), P3.15
A18: J1.52 (A18), P4.2
A19: J1.54 (A19), P4.4
A20: J1.56 (A20), P4.3
A21: J1.58 (A21), P4.6
A22: J1.57 (A22), P4.5
A23: J1.59 (A23), P4.8
AS: J1.74 (~AS), P3.4
BOOTSEL: J5.3, P2.5
BUSRST: J1.94 (~BUSRST), P4.9
CFGIN: J1.12 (~CFGIN), P4.7
CFGOUT: J1.11 (~CFGOUT), P4.10
D0: J1.75 (D0), P1.2
D1: J1.77 (D1), P1.4
D2: J1.79 (D2), P1.3
D3: J1.81 (D3), P1.6
D4: J1.83 (D4), P1.5
D5: J1.86 (D5), P1.8
D6: J1.84 (D6), P1.7
D7: J1.82 (D7), P1.10
D8: J1.80 (D8), P1.9
D9: J1.78 (D9), P1.12
D10: J1.76 (D10), P1.11
D11: J1.71 (D11), P1.14
D12: J1.69 (D12), P1.13
D13: J1.67 (D13), P1.16
D14: J1.65 (D14), P1.15
D15: J1.63 (D15), P3.2
GND: C1.2, C2.2, C3.2, C4.2, C5.2, C6.2, C101.2, C102.2, C103.2, C201.2, C202.2, C203.2, C204.2, C205.2, C301.2, C401.2, J1.1 (GND), J1.2 (GND), J1.3 (GND), J1.4 (GND), J1.13 (GND), J1.25 (GND), J1.37 (GND), J1.49 (GND), J1.61 (GND), J1.73 (GND), J1.85 (GND), J1.87 (GND), J1.88 (GND), J1.89 (GND), J1.90 (GND), J1.91 (GND(SENSEZ3)), J1.99 (GND), J1.100 (GND), J2.4 (GND), J2.SH (Shield), J3.7, J3.8, J4.2, J5.2, J6.6 (VSS), J6.SH (SHIELD), M1J1.1, M1J1.2, M1J2.1, M2.6, M3J1.1, M3J1.5, P1.1, P2.1, P2.8, P2.14, P3.1, P4.1, Q1.1 (E), Q101.2 (E), U2.1 (GND), U201.1 (GND)
I2S_BCK: M3J1.2, P2.4
I2S_DIN: M3J1.3, P4.15
I2S_LCK: M3J1.4, P2.3
INT_BASE: Q1.2 (B), Q101.1 (B), R1.2, R101.2
INT_COLL: JP1.2 (C), Q1.3 (C), Q101.3 (C)
INT_DRV: P2.2, R1.1, R101.1
NIC_CS: M1J1.5, P4.14
NIC_INT: M1J1.6, P4.12
unnamed: C401.1, R6.2
READ: J1.68 (READ), P3.5
RUN: J5.1, P2.11
SD_CS: J6.2 (DAT3/CD), M2.2, P3.6
SD_DAT1: J6.8 (DAT1), R5.2
SD_DAT2: J6.1 (DAT2), R2.2
SPI1_MISO: J6.7 (DAT0), M1J2.6, M2.5, P4.11, R4.2
SPI1_MOSI: J6.3 (CMD), M1J1.3, M2.3, P4.16, R3.2
SPI1_SCK: J6.5 (CLK), M1J1.4, M2.4, P4.13
SWCLK: J4.1, P2.10
SWDIO: J4.3, P2.6
UDS: J1.72 (~UDS), P3.3
USB_DM: J2.2 (D-), J3.3, P2.7
USB_DP: J2.3 (D+), J3.5, P2.9
VBUS_PORT: C2.1, C201.1, C202.1, C203.1, C204.1, C205.1, F1.2, F101.2, J2.1 (VBUS), J3.1, J3.2
VIN: D1.1 (K), D101.1 (K), M3J1.6, P2.15
XRDY: J1.18 (XRDY), P3.13
Z_INT2: J1.19 (~INT2), JP1.1 (A)
Z_INT6: J1.22 (~INT6), JP1.3 (B)

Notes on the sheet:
Zorro II edge connector (J1)
Card edge, 2x50 fingers. Pin 2 is rightmost seen from the component side. No series resistors, no buffers: every bus net goes straight to the module.
Pin 70 (/LDS) is not connected: GPIO18 is the microSD chip select here. The bus PIO programs wait on /AS and branch on READ only. With /UDS alone word access, Autoconfig and the rejection of an odd-byte write work; an even-byte write is taken as a word write. XRDY (18) comes straight from GPIO27 (3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
U1: Waveshare Core2350B B0 (RP2350B module, no PSRAM)
Four 2x8 pin strips P1-P4 round a 25.4 mm square, drawn here in the order of the GPIO numbers. GPIO0-17, 19-43 and 45 as in hardware/PINMAP.md. Different: GPIO18 microSD CS, GPIO44 / 46 / 47 I2S.
GPIO0-14
power, SWD, USB, GPIO45-47
GPIO15-29
GPIO30-44
P2: 5 BOOTSEL and 11 RUN to J5, 6 SWDIO and 10 SWCLK to J4, 7 / 9 USB D- / D+ to J2 and J3 (27R on the module). P2: 12 ADC_VREF and 13 3V3_EN not connected (3V3_EN open = module LDO on). P2.15 VBUS is the module's 5 V input (VIN, through D1); P2.16 its 3V3 output (ME6217C33 LDO), which also feeds M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
Power: bus +5 V only; D1 to the module, F1 to the USB port
The card is powered by the Amiga, or by the module's FPC adapter on the bench. The port never powers the card.
to U1 P2.15 and M3 VIN
to J2.1, J3.1, J3.2
JP2 OPEN as delivered. Bridge it only on a board without U2: +3V3 (U1 P2.16, module LDO) then feeds 3V3_AUX (M1, M2). U2 is fitted by default: JP2 stays open.
D1 1N5817 (DO-41) keeps bench power (the module's FPC USB adapter feeds the same VBUS net) off the Amiga's +5 V rail. F1 is all there is between the bus +5 V and the port: no series diode, no power switch IC. Resettable PTC, 0.9 A hold (trips at 1.8 A), 30 V or 16 V family, 5.08 mm leads: Littelfus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
Interrupt to the bus: Q1 NPN, open collector
GPIO45 high asserts the interrupt (push-pull, high = asserted: the drive of firmware feature int-nfet). JP1 is bridged 1-2 as delivered: /INT2. Cut 1-2 and bridge 2-3 for /INT6.
JP1 1 = /INT2 (J1 19, default) JP1 3 = /INT6 (J1 22)
Q1 2N3904, TO-92: emitter to GND, base through R1 (2.2k) to GPIO45, collector through JP1 to the bus. GPIO45 resets with its pull-down on: Q1 is off while the module is in reset; with the module absent the base is open and Q1 is off. A B2000 / A500+ pull the lines up with 1k (5 mA); the TRM's open-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
USB host port: J2 or J3 (fit one)
D+ / D- from U1 P2.9 / P2.7 (27R on the module) to J2 and J3 in parallel; only one of the two is used. VBUS_PORT from the bus +5 V through F1 (power block).
J2: type A, through-hole, right angle. Hole pattern of Molex 67643, Stewart SS-52100-001, Kycon KUSBX-AS1N, Connfly DS1095. 1 VBUS, 2 D-, 3 D+, 4 GND, shell to GND.
J3: 2x5, 2.54 mm, PC internal USB pinout. 1, 2 VBUS_PORT; 3 D-; 5 D+; 7, 8 GND. 9 is the key (pin absent). 4, 6 (a second port's data) and 10 (over-current sense on a PC): not connected. A slot bracket's first socket works, its second has power only. A 1x4 cable fits the odd row.
Pin map
module pin = header.pin; J1 = Zorro II finger. README.md, section Pin map, has the same table
GPIO GPIO0 GPIO1 GPIO2 GPIO3 GPIO4 GPIO5 GPIO6 GPIO7 GPIO8 GPIO9 GPIO10 GPIO11 GPIO12 GPIO13 GPIO14 GPIO15 GPIO16 GPIO17 GPIO18 GPIO19 GPIO20 GPIO21 GPIO22 GPIO23 GPIO24 GPIO25 GPIO26 GPIO27 GPIO28 GPIO29 GPIO30 GPIO31 GPIO32 GPIO33 GPIO34 GPIO35 GPIO36 GPIO37 GPIO38 GPIO39 GPIO40 GPIO41 GPIO42 GPI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
module pin P1.2 P1.4 P1.3 P1.6 P1.5 P1.8 P1.7 P1.10 P1.9 P1.12 P1.11 P1.14 P1.13 P1.16 P1.15 P3.2 P3.4 P3.3 P3.6 P3.5 P3.8 P3.7 P3.10 P3.9 P3.12 P3.11 P3.14 P3.13 P3.16 P3.15 P4.2 P4.4 P4.3 P4.6 P4.5 P4.8 P4.7 P4.10 P4.9 P4.12 P4.11 P4.14 P4.13 P4.16 P4.15 P2.2 P2.4 P2.3
net D0 D1 D2 D3 D4 D5 D6 D7 D8 D9 D10 D11 D12 D13 D14 D15 AS UDS SD_CS READ A1 A2 A3 A4 A5 A6 A7 XRDY A16 A17 A18 A19 A20 A21 A22 A23 CFGIN CFGOUT BUSRST NIC_INT SPI1_MISO NIC_CS SPI1_SCK SPI1_MOSI I2S_DIN INT_DRV I2S_BCK I2S_LCK
goes to J1 75 J1 77 J1 79 J1 81 J1 83 J1 86 J1 84 J1 82 J1 80 J1 78 J1 76 J1 71 J1 69 J1 67 J1 65 J1 63 J1 74 J1 72 M2.2 / J6.2 J1 68 J1 29 J1 27 J1 26 J1 24 J1 21 J1 23 J1 28 J1 18 J1 45 J1 47 J1 52 J1 54 J1 56 J1 58 J1 57 J1 59 J1 12 J1 11 J1 94 M1J1.6 M1J2.6, M2.5 / J6.7 M1J1.5 M1J1.4, M2.4 / J6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
DIY build (default variant): U1, M1, D1, F1, C1, C2, Q1, R1, J2 or J3. Optional: M2 (microSD), M3 (DAC). U2, C3, C4 fitted (3V3_AUX regulator; JP2 open). Not fitted (DNP): J4 (developers), J5 (recovery). JLC build (variant JLC): the SMD parts of block 11 instead of D1, F1, C1-C4, Q1, R1, U2 and M2;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
M1: W5500 "Lite" module (USR-ES1, WIZ850io pinout)
Two 1x6 rows, 2.54 mm, 20.32 mm apart, drawn as seen from the top with the jack opening away from the viewer. Pin 1 of each row at the jack-opening end. Module silk: J1 left row (M1J1), J2 right row (M1J2).
GND
MOSI
SCLK
SCNn
INTn
3.3V
RSTn

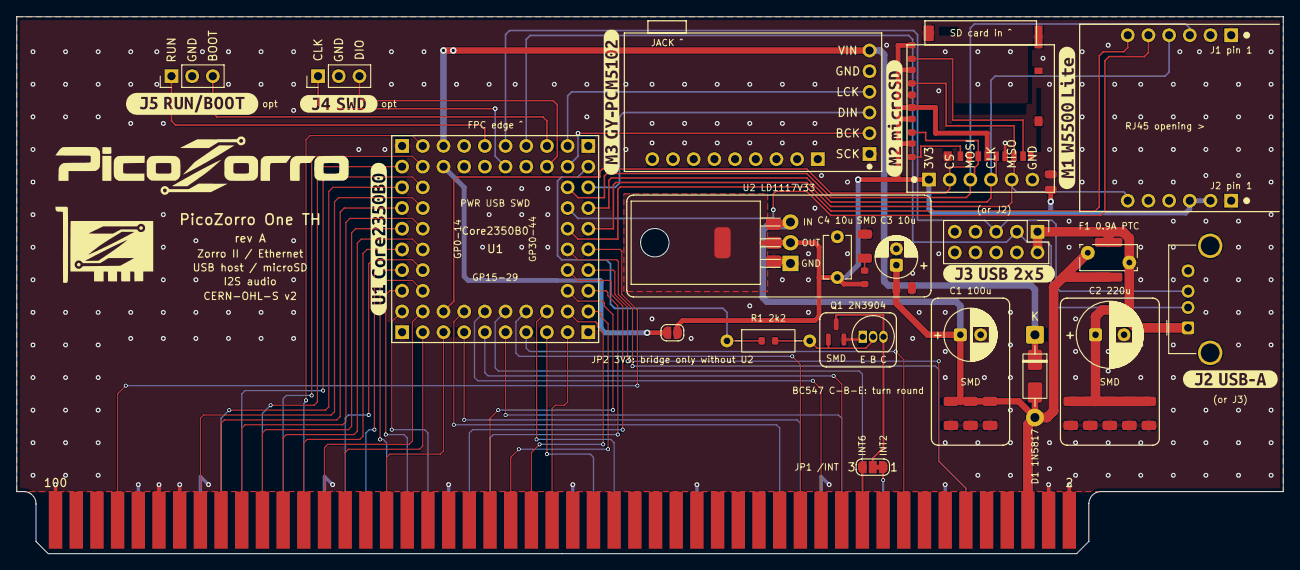
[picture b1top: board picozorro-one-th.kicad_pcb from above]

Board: 2 copper layers, 155.5 x 65.9 mm, 48 parts (0 on the bottom side), 67 nets.

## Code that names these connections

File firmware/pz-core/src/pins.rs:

//! GPIO numbers, `hardware/PINMAP.md`. One map for every board and firmware.

pub const D0: u8 = 0; // D0..D15 = GPIO0..15
pub const AS: u8 = 16; // active low
pub const UDS: u8 = 17; // active low
pub const LDS: u8 = 18; // active low
pub const READ: u8 = 19; // high = read
pub const A1: u8 = 20; // A1..A7 = GPIO20..26
pub const XRDY: u8 = 27; // open drain: value 0, switched by direction
pub const A16: u8 = 28; // A16..A23 = GPIO28..35
pub const CFGIN: u8 = 36; // active low; 9th bit of the match field
pub const CFGOUT: u8 = 37; // active low, push-pull
pub const BUSRST: u8 = 38; // active low
pub const ARM: u8 = 44; // active low, gate-assist option
pub const UART_TX: u8 = 46;

/// /INT to the Amiga: open drain by direction through an open-drain buffer,
/// or push-pull into an N-MOSFET (pz-app feature `int-nfet`, the PicoZorro
/// One TH). A jumper on the board picks /INT2 or /INT6.
pub const INT: u8 = 45;

/// Activity LED where there is one (the Core2350B module's LED1 via R10), and
/// the W5500 /INT input: the same pin. The W5500's INTn is push-pull
/// (VOH >= 2.4 V at 8 mA), so it drives the LED itself; with a W5500 attached
/// the pin is an input, without one the firmware may drive the LED.
pub const LED: u8 = 39;

/// SPI1 to the Ethernet chip (function F1 on these pins).
pub const NIC_MISO: u8 = 40;
pub const NIC_CS: u8 = 41;
pub const NIC_SCK: u8 = 42;
pub const NIC_MOSI: u8 = 43;
/// W5500 /INT (INTn), active low. Shares GPIO39 with the LED. GPIO47 is
/// never used: on the Core2350B it is the module's PSRAM chip select (R11).
pub const NIC_INT: u8 = LED;

pub const BUS_PIN_FIRST: u8 = 0;
/// /INT (GPIO45) is set up on its own.
pub const BUS_PIN_LAST: u8 = 38;

/// Layout of the 29-bit cycle word captured by PIO block A (`in pins, 29`):
/// GPIO0-28, i.e. D15-D0, the strobes, A7-A1, XRDY (ignored) and A16.
pub mod cw {
    pub const AS: u32 = 1 << 16;
    pub const UDS: u32 = 1 << 17;
    pub const LDS: u32 = 1 << 18;
    pub const READ: u32 = 1 << 19;
    pub const A16: u32 = 1 << 28;
    pub const BITS: u32 = 29;
    pub fn data(w: u32) -> u16 {
        w as u16
    }
    /// Even byte offset (A7..A1).
    pub fn reg(w: u32) -> u8 {
        (((w >> 20) & 0x7f) << 1) as u8
    }
    /// A16: the second 64 KiB of the board (USB, MPEG, update).
    pub fn a16(w: u32) -> bool {
        w & A16 != 0
    }
}

/// Match field seen by block B while unconfigured: {CFGIN, A23..A16}.
/// CFGIN low = bit 8 clear.
pub const MATCH_BITS: u32 = 9;
/// No sample can equal this.
pub const MATCH_NEVER: u32 = 0xffff_ffff;
/// $E8xxxx with /CFGIN asserted.
pub const MATCH_CONFIG: u32 = 0x0e8;
/// Configured, the board is 128 KiB and A16 is not compared: block B reads
/// {CFGIN, A23..A17} from A17 on.
pub const MATCH_BITS_CONFIGURED: u32 = 8;
/// First pin of the configured match field.
pub const MATCH_BASE_CONFIGURED: u8 = A16 + 1;
/// Match value for a board configured at `base` (A23..A16; A16 is 0 for a
/// 128 KiB board), /CFGIN asserted.
pub const fn match_configured(base: u8) -> u32 {
    (base >> 1) as u32
}

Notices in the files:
hardware/picozorro-one-th/picozorro-one-th.kicad_pcb:
PicoZorro (CERN-OHL-S v2)
CERN-OHL-S v2
